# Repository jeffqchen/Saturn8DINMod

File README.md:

## For better organized documentation, please refer to the [Project Wiki](../../wiki/)

----------------

# Sega Saturn 8-pin mini DIN Mod

This is a mod design with a PCB and a 3D printed shroud, for replacing a broken 10-pin mini DIN AV port on a Sega Saturn with an 8-pin mini DIN port. It will output an RGBS video signal and stereo audio, conforming to the XRGB pinout.

This design has been verified on NTSC model HST-3210 and HST-3220, as well as the Victor V-Saturn RG-JX2(Y). If your Saturn is from a different model, the metal shield might be incompatible with the 3D-printed piece. You might need to trim the piece or your metal shield in order for it to fit (or you could provide me with some measurements so I can design a compatible one.)

**Note: the CSync signal is not available on PAL models. Do NOT populate the CSync portion of the PCB and instead use Luma for sync.**

-------------
## Explanation

The Sega Saturn opted for a strange 10-pin mini DIN connector for its AV output. Decades of abuse and oxidation has rendered a lot of them inoperable. Some horror story has it shorting +5V to GND internally, almost killing the machine itself.

*Flaky old 10-pin mini DIN*

"Just replace it with a new one!" You may say. But looking around the internet, it's impossible to find an exact replacement 10-pin mini DIN female socket.

On the other hand, if you want to hook up a Saturn to your setup, you will need a 10-pin AV cable. This cable will only work with the Saturn since no other device uses the same type of connection. Bummer. This cable is also known for it's flaky connection. Accidentally sneeze on it, your picture turns blue and you lose an audio channel. To add salt to injury, there is no way to buy that male 10-pin mini DIN plug either, even if you plan to build your own dream cable. Oof.

Meanwhile, 8-pin mini DIN sockets are eye-watering cheap and abundantly available on Aliexpress 🤡

This is why I made this decision - the 10-pin mini DIN connector has to go.

Looking at the Saturn's schematic, its RGB lines are properly DC-decoupled with 220uF caps. Its CSync line needs to be attenuated and DC-decoupled for normal 75 ohm devices. This is very similar to an XRGB 8-pin DIN video cable, which is just straight pass-throughs with no extra components.

Consoles that use 8-pin mini DIN RGBS cables that I am aware of:
- NESRGB (8-pin mini DIN version)
- 3DORGB
- Supergun Minigun

If you have a cable for any of these devices above, you are already set!

*[Mini-DIN 8p to RGB SCART adapter](https://etim.net.au/shop/shop.php?crn=203&rn=543&action=show_detail) from Tim Worthington*

Retro Gaming Cables from UK sells a cable that's similar to Tim's cable [Here](https://www.retrogamingcables.co.uk/8PIN-MINI-DIN-TO-RGB-EUROSCART-TIM-WORTHINGTON-NES-RGB-ATARI-2600-HAS-SUPERGUN-Sega-Game-Gear-Philips-CDi-Colecovision-Intellivision-Panasonic-3DO).

Retro Access sells an [XRGB to BNC adapter](https://retro-access.com/collections/xrgb-adaptors/products/bnc-to-8-pin-mini-din-for-extron-to-xrgb-mini-pro-coaxial-multicore?variant=45853115731).

Since this port conforms to the XRGB standard, the signal can go straight into the RGB IN port on a Framemeister with an 8-pin mini DIN cable.

But of course, if you don't have any of those above, you can still build my [8DIN2VGA dongle](https://github.com/jeffqchen/8DIN2VGA) and output from a VGA cable!

-------------
## Parts

- [Saturn 8-pin mini DIN Mod PCB](https://oshpark.com/shared_projects/etx4c03R)
- 8-pin mini DIN Female Socket

For Attenuated CSync:
- SMD Capacitor 220uF / 6.3V / Imperial 1206 Size - [Link](https://github.com/jeffqchen/JeffParts/blob/main/Components/220uF%20SMD%20Cap/info.md)
- SMD Resistor 470 Ohm / Imperial 0603 Size (for 75 Ohm CSync, otherwise zero Ohm)

-------------
## 3D Printing

Print the model as-is without support. Easy and simple.

-------------
## Port Assembly

Clean up the perimeter of the PCB so nothing is sticking out.

Populate the PCB. Choose one from these 3 options.

- For attenuated 75 Ohm CSync: (NTSC Only)
  - Solder the 220uF capacitor and the 470 Ohm resistor on to the PCB

- For unattenuated CSync: (NTSC Only)
  - Populate the 220uF capacitor, short the resistor footprint with a blob of solder or 0 Ohm SMD resistor.

- For Luma as Sync: (NTSC & PAL)
  - Close the "Luma Sync" jumper. Do not populate any SMD component.

Note: When soldering the 220uF SMD cap, make sure the solder does NOT short the adjacent jumper pad.

Then, tin all the SMD pads on both sides pf the PCB with a good amount of solder, so you can solder metal pins onto them.

### Tips For Soldering Pins Onto The PCB

#### Method

Here is a method suggested by [Leon Kiriliuk](https://twitter.com/leonkiriliuk/status/1542005845776547842), and I find it makes a ton of sense. Unfortunately I ran out of the Saturn PCB at the time, so I used a piece of prototype board as a demonstration.

First, pick a sacrificial resistor with long legs. I bent the legs into a zigzag shape with a syringe needle, with each section about 5mm long. This will be the length we need for the pins. You could also simply mark the length with a marker pen. It's all up to you.

Holding the resistor body, solder the end to the pad.

Then, cut it with a side cutter.

Repeat the process.

Correct any crooked pins with the needle. I find it very easy to bend and correct pins with a syringe needle. Sometimes I use this method to bend chip pins,   including CPU pins.

#### Lead-Free Solder Consideration

Since we are going to solder the other end of these pins to the Saturn motherboard, these pins will be heated again. Sometimes this will cause this end of the pins to fall off the small PCB.

It might be a good idea to use lead-free solder during this step, so the higher melting point will protect these solder joints during the final soldering step.

-------------
## Solder in the 8-pin mini DIN port

With all the pins soldered to both sides of the PCB, we can proceed.

Before trying to feed the 8-pin mini DIN socket into the 3D printed piece, bend the shielding pins on the two side slightly outwards.

Feed the 8-pin mini DIN socket from the front of the 3D-printed piece. For now, push it in only so that the pins on the back is flush with the hole on the back.

Lay the PCB on the back of the 3D printed piece. Lodge the cutout on the PCB into the sticking out piece on the left side of the shroud at an angle, then close it down so it sits inside the brackets on the right side.

Then feed the pins on the back of the 8-pin DIN through the holes on the PCB, and press the DIN port all the way in. Its rim should sit flush with the face of the piece once pushed all the way in.

If you have problems with the pins going through the vias, especially the shielding pins on the sides, use a pair of tweezers to help guiding those pins through from the gap between the PCB and the 3D printed shroud. This is why I suggested to bend the shield pins slightly outwards before hand.

Make sure everything is tightly pressed together, then solder down at least two pins onto the PCB. Keep checking if it's tight and snug. Melt the soldered pin if you have to adjust. Then, solder in the rest of the pins on the 8-pin DIN.

-------------
## 10-pin mini DIN Removal

*This is my method WITHOUT using a desoldering gun. If you have a desoldering gun, feel free to proceed with your own ordinary method!*

Reflow every pin on the 10-pin DIN with some fresh solder. Push and wiggle the pins to exercise the solder inside the vias so that it's thoroughly reflowed.

Suck up as much as possible solder from each of the pins with solder wick. Wiggle the pins by pushing them around with the solder wick while heating it up with the iron to make sure you remove as much as the solder you can.

Then with a pair of pliers holding the 10 pin DIN from below (but not pulling YET), blast the pins directly with hot air from the top.

Wait until the solder start to melt. Then you will be able to wiggle and pull the 10-pin DIN out without too much resistance. IF you feel that you are pulling too hard and the PCB started to warp, STOP. This means your solder is not melted enough. And you will likely cause a lot of damage to the board. Be patient and give it a bit more time to melt properly.

Finally, clean up the bottom of the PCB with some alcohol.

-------------
## Installation onto Saturn motherboard

Feed the assembled 8-pin DIN through the holes on the Saturn motherboard. Be careful and patient so you don't feel the leads through wrong holes.

Make sure the 3D-printed piece sits tightly against the PCB. Note the front and back face of the DIN is NOT perpendicular with the PCB. This is intended. Otherwise the new 8-pin DIN port will not sit flush with the Saturn outer shell, but instead have an ugly gap.

Solder in the two outside pins so the assembly is held down. You can melt them again if the assembly does not sit properly in its place. Keep adjusting until you are satisfied.

Solder in one row of the signal pins, then trim them.

Solder in the other row of signal pins, and trim them too.

And installation is finished.

-------------
## Closing Up

You can now put the Saturn back together like normal.

Note when you try to sit the motherboard back into its place, the 8-pin DIN needs a firm press so it snaps into the hole snuggly with an audible click.

When laying the top metal shield back into its place, make sure the metal tongues sit nicely into the slots on the 3D-printed piece.

With the help of the outer shell, the PCB and the metal shielding, there is no wiggle room for the new port. I expect it to be as sturdy as the original, if not better.

Enjoy your Saturn with an 8-pin mini DIN AV port!

-------------
## Special Thanks
Leon Kiriliuk
- Twitter: https://twitter.com/leonkiriliuk

-------------
Shield: [![CC BY-SA 4.0][cc-by-sa-shield]][cc-by-sa]

This work is licensed under a
[Creative Commons Attribution-ShareAlike 4.0 International License][cc-by-sa].

[![CC BY-SA 4.0][cc-by-sa-image]][cc-by-sa]

[cc-by-sa]: http://creativecommons.org/licenses/by-sa/4.0/
[cc-by-sa-image]: https://licensebuttons.net/l/by-sa/4.0/88x31.png
[cc-by-sa-shield]: https://img.shields.io/badge/License-CC%20BY--SA%204.0-lightgrey.svg

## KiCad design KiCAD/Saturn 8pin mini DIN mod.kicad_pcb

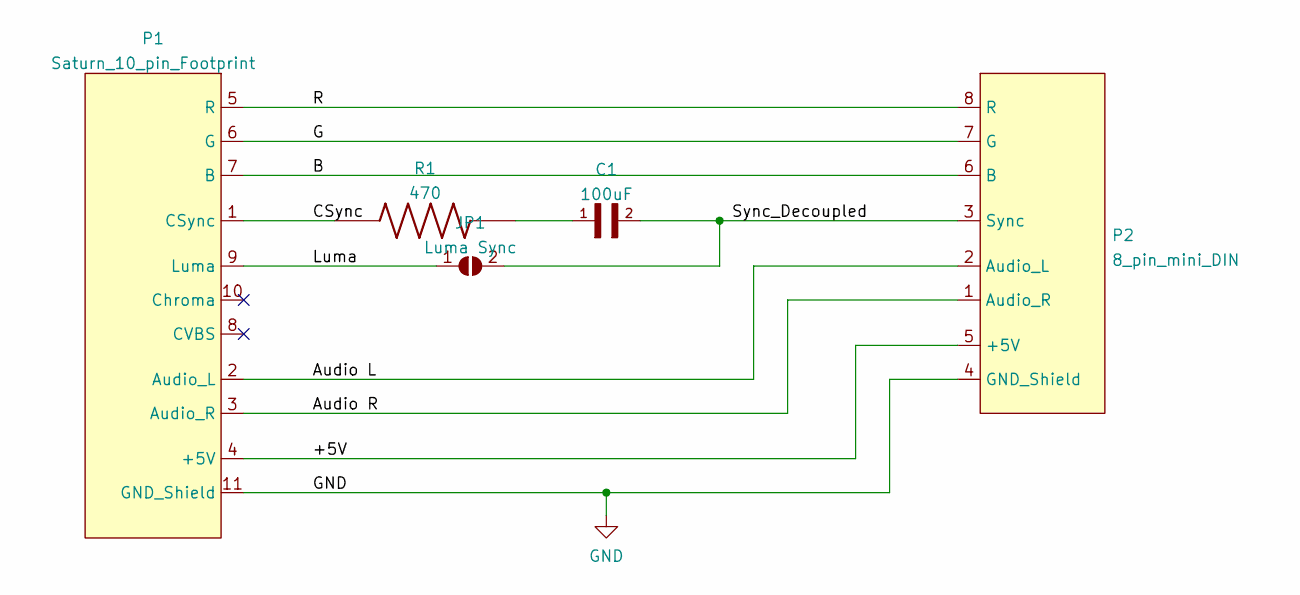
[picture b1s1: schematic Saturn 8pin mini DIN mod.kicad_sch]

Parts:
C1: 100uF; C_1206_3216Metric
JP1: Luma Sync; SolderJumper-2_P1.3mm_Open_RoundedPad1.0x1.5mm
P1: Saturn_10_pin_Footprint; Saturn 10 pin
P2: 8_pin_mini_DIN; 8 pin mini DIN
R1: 470; R_0603_1608Metric

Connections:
/+5V: P1.4 (+5V), P2.5 (+5V)
/Audio L: P1.2 (Audio_L), P2.2 (Audio_L)
/Audio R: P1.3 (Audio_R), P2.1 (Audio_R)
/B: P1.7 (B), P2.6 (B)
/CSync: P1.1 (CSync), R1.1
/G: P1.6 (G), P2.7 (G)
/Luma: JP1.1 (A), P1.9 (Luma)
/R: P1.5 (R), P2.8 (R)
/Sync_Decoupled: C1.2, JP1.2 (B), P2.3 (Sync)
GND: P1.11 (GND_Shield), P2.4 (GND_Shield)
unnamed: C1.1, R1.2

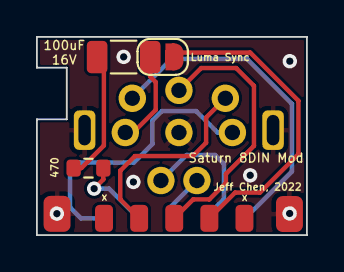
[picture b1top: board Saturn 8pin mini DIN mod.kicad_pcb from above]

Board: 2 copper layers, 15.0 x 11.0 mm, 5 parts (0 on the bottom side), 11 nets.

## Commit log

2022-07-05 Add XRGB pinout
2022-07-05 Add 8din photo
2022-07-05 Upload KiCAD files
2022-07-11 Duplicate pics for wiki
2022-07-11 Remove pics
2022-08-09 Change license type
